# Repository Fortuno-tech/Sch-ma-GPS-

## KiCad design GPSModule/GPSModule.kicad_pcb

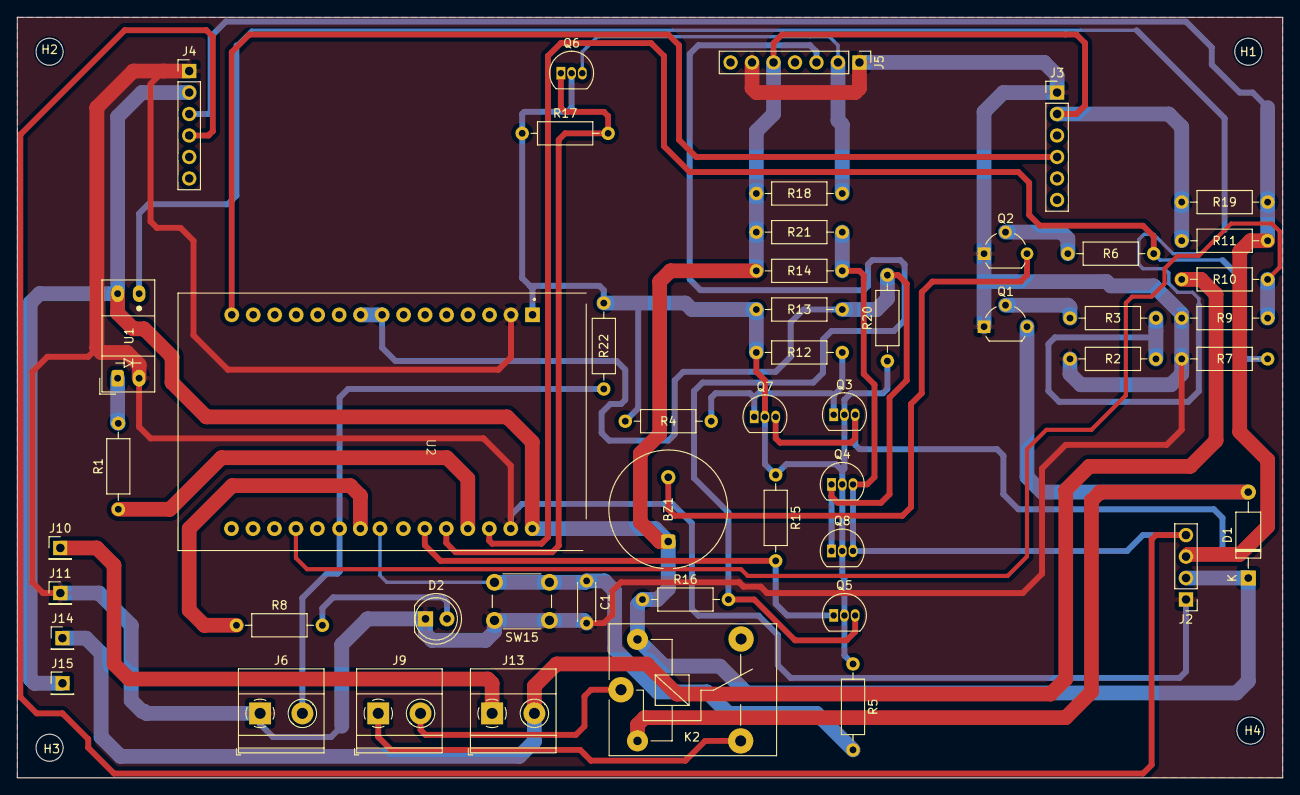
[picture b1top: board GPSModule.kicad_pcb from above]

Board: 2 copper layers, 149.6 x 89.9 mm, 53 parts (0 on the bottom side), 29 nets.

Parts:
BZ1: Buzzer; Indicator_PUI_AI-1440-TWT-24V-2-R
C1: C; C_Disc_D4.3mm_W1.9mm_P5.00mm
D1: 1N914WT; D_A-405_P10.16mm_Horizontal
D2: LED; LED_D5.0mm
H1, H2, H3, H4: MountingHole_Pad; MountingHole_3.2mm_M3_ISO7380
J2: RFID PN532; PinHeader_1x04_P2.54mm_Vertical
J3: SD_CARD; PinHeader_1x06_P2.54mm_Vertical
J4: DS3231; PinHeader_1x06_P2.54mm_Vertical
J5: SIM7600; PinHeader_1x07_P2.54mm_Vertical
J6, J9, J13: S; TerminalBlock_Phoenix_MKDS-1,5-2_1x02_P5.00mm_Horizontal
J10, J11, J14, J15: Conn_01x04; PinHeader_1x01_P2.54mm_Vertical
K2: SANYOU_SRD_Form_C; Relay_SPDT_SANYOU_SRD_Series_Form_C
Q1, Q2: 2SC1941; TO-92L_Wide
Q3, Q4, Q5, Q6, Q7, Q8: 2N7000; TO-92_Inline
R1, R3, R6: 330; R_Axial_DIN0207_L6.3mm_D2.5mm_P10.16mm_Horizontal
R2, R4, R5, R8, R11, R12, R13, R14, R15, R16, R17, R18, R19, R20, R21, R22: 10K; R_Axial_DIN0207_L6.3mm_D2.5mm_P10.16mm_Horizontal
R7: 10ΚΩ; R_Axial_DIN0207_L6.3mm_D2.5mm_P10.16mm_Horizontal
R9: 10KΩ; R_Axial_DIN0207_L6.3mm_D2.5mm_P10.16mm_Horizontal
R10: 62KΩ; R_Axial_DIN0207_L6.3mm_D2.5mm_P10.16mm_Horizontal
SW15: SW_MEC_5G; SW_PUSH_6mm_H8mm
U1: VO615A-1; Everlight_ITR9608-F
U2: ESP32-DEVKIT-V1; ESP32 DEVKIT V1

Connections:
+3.3V: Q3.2 (G), Q4.2 (G), Q5.2 (G), Q6.2 (G), Q7.2 (G), Q8.2 (G), R4.1, R5.1, R12.1, R13.1, R15.1, R17.1, R20.1, R22.2, U2.19 (3V3)
+5V: BZ1.1 (-), D1.1 (K), J2.2, J3.2, J4.2, J5.5, J15.1, K2.5, R11.1, R14.1, R16.1, R18.1, R19.1, R21.1, U1.4, U2.18 (VIN)
/BT +: J13.2, J14.1, R10.2
/D12: R1.1, U2.12 (GPIO12_ADC2-CH5_HSPI-MISO_RTC-GPIO15)
/D13: R6.2, R7.2, U2.13 (GPIO13_ADC2-CH4_HSPI-MOSI_RTC-GPIO14)
/D14: Q6.1 (S), R17.2, U2.11 (GPIO14_ADC2-CH6_HSPI-CLK_RTC-GPIO16)
/D14°: J5.2, Q6.3 (D), R18.2
/D21: Q3.1 (S), Q7.1 (S), R4.2, R12.2
/D21°: J2.3, J4.3, Q3.3 (D), Q7.3 (D), R11.2, R19.2
/D22: Q4.1 (S), Q8.1 (S), R13.2, R20.2, U2.35 (GPIO22_I2C-SCL)
/D22°: J2.4, J4.4, Q4.3 (D), Q8.3 (D), R14.2, R21.2
/D23: J3.4, U2.36 (GPIO23_VSPI-MOSI)
/D25: C1.1, R5.2, SW15.3 (B), U2.8 (GPIO25_ADC2-CH8_DAC1_RTC-GPIO6)
/D27: Q5.1 (S), R15.2, U2.10 (GPIO27_ADC2-CH7_RTC-GPIO17)
/D27°: J5.3, Q5.3 (D), R16.2
/D32: J6.2, R22.1, U2.6 (GPIO32_ADC1-CH4_RTC-GPIO9)
/D33: R8.1, U2.7 (GPIO33_ADC1-CH5_RTC-GPIO8)
/D34: R9.2, R10.1, U2.4 (GPIO34_ADC1-CH6_RTC-GPIO4)
GND: C1.2, D2.1 (K), J2.1, J3.1, J4.1, J5.1, J5.6, J6.1, J11.1, Q1.1 (E), Q2.1 (E), R2.2, R7.1, R9.1, SW15.1 (A), U1.2, U2.17 (GND)
unnamed: BZ1.2 (+), Q2.2 (C)
unnamed: D1.2 (A), K2.2, Q1.2 (C)
unnamed: D2.2 (A), R8.2
unnamed: J9.1, K2.3
unnamed: J9.2, K2.1
unnamed: J10.1, J13.1
unnamed: Q1.3 (B), R3.1
unnamed: Q2.3 (B), R6.1
unnamed: R1.2, U1.1
unnamed: R2.1, R3.2, U1.3

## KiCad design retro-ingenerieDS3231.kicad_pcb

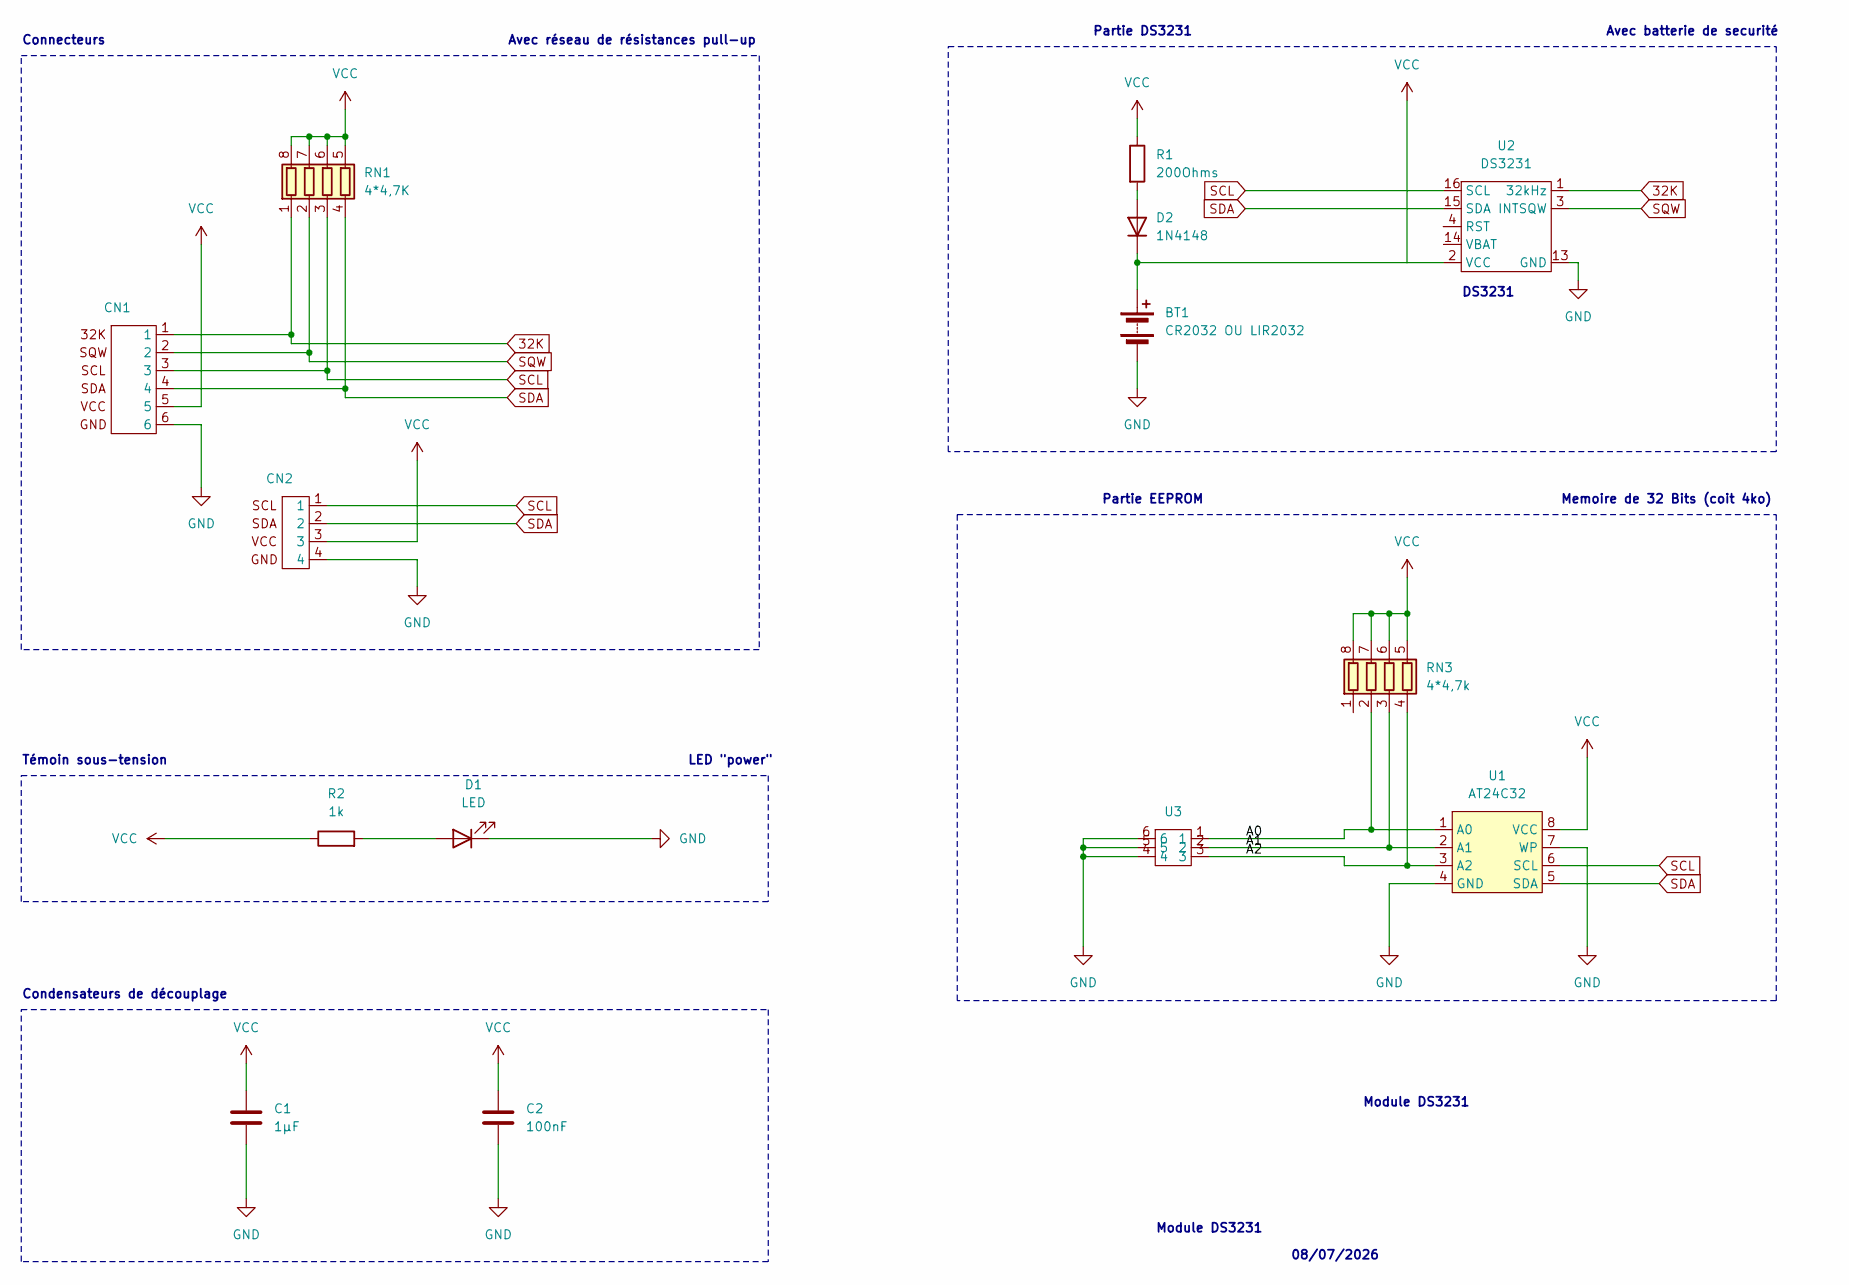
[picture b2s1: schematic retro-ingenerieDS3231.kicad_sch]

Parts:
BT1: CR2032 OU LIR2032; BatteryHolder_Keystone_1060_1x2032
C1: 1µF; C_0805_2012Metric
C2: 100nF; C_0805_2012Metric
CN1: PinHeader_1x06_P2.54mm_Vertical
CN2: PinHeader_1x04_P2.54mm_Vertical
D1: LED; LED_0805_2012Metric
D2: 1N4148; D_SOD-123
R1: 200Ohms; R_0805_2012Metric
R2: 1k; R_0805_2012Metric
RN1: 4*4,7K; R_Array_Convex_4x0603
RN3: 4*4,7k; R_Array_Convex_4x0603
U1: AT24C32; SOIC -8
U2: DS3231; SOIC -16
U3: EEPROM_Adress_Selector_3xSJ

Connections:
32K: CN1.1, RN1.1 (R1.1), U2.1 (32kHz)
/A0: RN3.2 (R2.1), U1.1 (A0), U3.1
/A1: RN3.3 (R3.1), U1.2 (A1), U3.2
/A2: RN3.4 (R4.1), U1.3 (A2), U3.3
GND: BT1.2 (-), C1.1, C2.1, CN1.6, CN2.4, D1.1 (K), U1.4 (GND), U1.7 (WP), U2.13 (GND), U3.4, U3.5, U3.6
unnamed: BT1.1 (+), D2.1 (K), U2.2 (VCC)
unnamed: D1.2 (A), R2.2
unnamed: D2.2 (A), R1.2
SCL: CN1.3, CN2.1, RN1.3 (R3.1), U1.6 (SCL), U2.16 (SCL)
SDA: CN1.4, CN2.2, RN1.4 (R4.1), U1.5 (SDA), U2.15 (SDA)
SQW: CN1.2, RN1.2 (R2.1), U2.3 (INTSQW)
VCC: C1.2, C2.2, CN1.5, CN2.3, R1.1, R2.1, RN1.5 (R4.2), RN1.6 (R3.2), RN1.7 (R2.2), RN1.8 (R1.2), RN3.5 (R4.2), RN3.6 (R3.2), RN3.7 (R2.2), RN3.8 (R1.2), U1.8 (VCC)

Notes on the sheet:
Avec batterie de securité
Condensateurs de découplage
Module DS3231
Partie DS3231
Avec réseau de résistances pull-up
DS3231
Partie EEPROM
Connecteurs
Témoin sous-tension
08/07/2026
Memoire de 32 Bits (coit 4ko)
LED "power"

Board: 2 copper layers, 14 parts (0 on the bottom side), 12 nets, no tracks yet.
